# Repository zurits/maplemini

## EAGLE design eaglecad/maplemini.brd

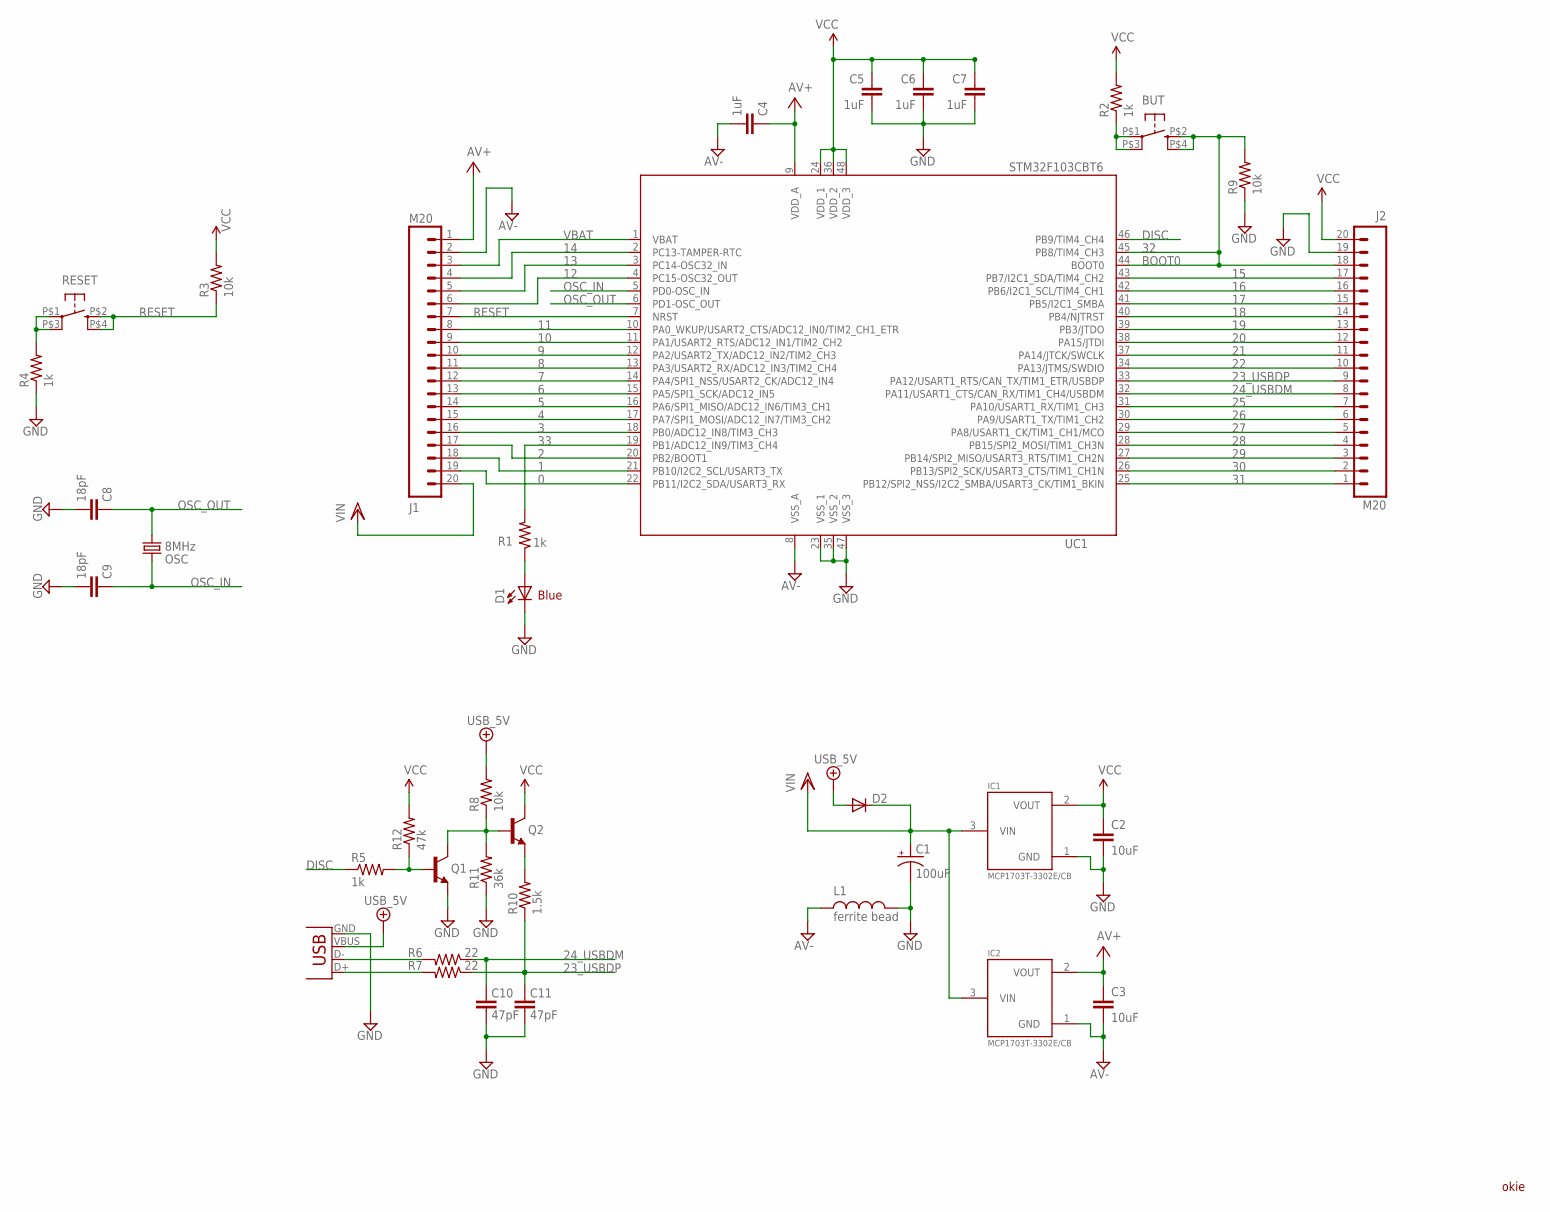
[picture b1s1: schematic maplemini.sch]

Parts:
BUT: KMR211GLFS; PUSHBUTTON-KMR241GLFS
C1: 100uF; EIA3216
C2, C3: 10uF; 0805
C4, C5, C6, C7: 1uF; C0402
C8, C9: 18pF; C0402
C10, C11: 47pF; C0402
D1: Blue; LED-1206
D2: DIODESOD; SOD-323
IC1, IC2: MCP1703T-3302E/CB; SOT23
J1, J2: M20; 1X20
L1: ferrite bead; 0603
OSC: 8MHz; CRYSTAL-SMD-5X3
Q1, Q2: NPN-BJT; SOT23
R1, R2, R4, R5: 1k; C0402
R3, R8, R9: 10k; C0402
R6, R7: 22; C0402
R10: 1.5k; C0402
R11: 36k; C0402
R12: 47k; C0402
RESET: KMR211GLFS; PUSHBUTTON-KMR241GLFS
UC1: STM32F103CBT6; LQFP48
X1: USB-MINIB

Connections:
0: J1.19, UC1.22 (PB11/I2C2_SDA/USART3_RX)
1: J1.18, UC1.21 (PB10/I2C2_SCL/USART3_TX)
2: J1.17, UC1.20 (PB2/BOOT1)
3: J1.16, UC1.18 (PB0/ADC12_IN8/TIM3_CH3)
4: J1.15, UC1.17 (PA7/SPI1_MOSI/ADC12_IN7/TIM3_CH2)
5: J1.14, UC1.16 (PA6/SPI1_MISO/ADC12_IN6/TIM3_CH1)
6: J1.13, UC1.15 (PA5/SPI1_SCK/ADC12_IN5)
7: J1.12, UC1.14 (PA4/SPI1_NSS/USART2_CK/ADC12_IN4)
8: J1.11, UC1.13 (PA3/USART2_RX/ADC12_IN3/TIM2_CH4)
9: J1.10, UC1.12 (PA2/USART2_TX/ADC12_IN2/TIM2_CH3)
10: J1.9, UC1.11 (PA1/USART2_RTS/ADC12_IN1/TIM2_CH2)
11: J1.8, UC1.10 (PA0_WKUP/USART2_CTS/ADC12_IN0/TIM2_CH1_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)
12: J1.6, UC1.4 (PC15-OSC32_OUT)
13: J1.5, UC1.3 (PC14-OSC32_IN)
14: J1.4, UC1.2 (PC13-TAMPER-RTC)
15: J2.17, UC1.43 (PB7/I2C1_SDA/TIM4_CH2)
16: J2.16, UC1.42 (PB6/I2C1_SCL/TIM4_CH1)
17: J2.15, UC1.41 (PB5/I2C1_SMBA)
18: J2.14, UC1.40 (PB4/NJTRST)
19: J2.13, UC1.39 (PB3/JTDO)
20: J2.12, UC1.38 (PA15/JTDI)
21: J2.11, UC1.37 (PA14/JTCK/SWCLK)
22: J2.10, UC1.34 (PA13/JTMS/SWDIO)
23_USBDP: C11.2, J2.9, R7.1, R10.1, UC1.33 (PA12/USART1_RTS/CAN_TX/TIM1_ETR/USBDP)
24_USBDM: C10.2, J2.8, R6.1, UC1.32 (PA11/USART1_CTS/CAN_RX/TIM1_CH4/USBDM)
25: J2.7, UC1.31 (PA10/USART1_RX/TIM1_CH3)
26: J2.6, UC1.30 (PA9/USART1_TX/TIM1_CH2)
27: J2.5, UC1.29 (PA8/USART1_CK/TIM1_CH1/MCO)
28: J2.4, UC1.28 (PB15/SPI2_MOSI/TIM1_CH3N)
29: J2.3, UC1.27 (PB14/SPI2_MISO/USART3_RTS/TIM1_CH2N)
30: J2.2, UC1.26 (PB13/SPI2_SCK/USART3_CTS/TIM1_CH1N)
31: J2.1, UC1.25 (PB12/SPI2_NSS/I2C2_SMBA/USART3_CK/TIM1_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)
32: BUT.P$2 (2), BUT.P$4 (4), J2.18, R9.2, UC1.44 (BOOT0), UC1.45 (PB8/TIM4_CH3)
33: R1.2, UC1.19 (PB1/ADC12_IN9/TIM3_CH4)
+5V/2: D2.2 (A), R8.2, X1.VBUS
AV+: C3.1, C4.1, IC2.2 (VOUT), J1.1, UC1.9 (VDD_A)
AV-: C3.2, C4.2, IC2.1 (GND), J1.2, L1.1, UC1.8 (VSS_A)
DGND: C1.C (-), C2.2, C5.2, C6.2, C7.2, C8.2, C9.2, C10.1, C11.1, D1.C, IC1.1 (GND), J2.19, L1.2, Q1.2 (E), R4.1, R9.1, R11.1, UC1.23 (VSS_1), UC1.35 (VSS_2), UC1.47 (VSS_3), X1.GND
DISC: R5.1, UC1.46 (PB9/TIM4_CH4)
unnamed: BUT.P$1 (1), BUT.P$3 (3), R2.1
unnamed: D1.A, R1.1
unnamed: R4.2, RESET.P$1 (1), RESET.P$3 (3)
unnamed: Q2.2 (E), R10.2
unnamed: R6.2, X1.D-
unnamed: R7.2, X1.D+
unnamed: Q1.3 (C), Q2.1 (B), R8.1, R11.2
unnamed: Q1.1 (B), R5.2, R12.1
OSC_IN: C9.1, OSC.3 (2), UC1.5 (PD0-OSC_IN)
OSC_OUT: C8.1, OSC.1, UC1.6 (PD1-OSC_OUT)
RESET: J1.7, R3.1, RESET.P$2 (2), RESET.P$4 (4), UC1.7 (NRST)
VBAT: J1.3, UC1.1 (VBAT)
VCC: C2.1, C5.1, C6.1, C7.1, IC1.2 (VOUT), J2.20, Q2.3 (C), R2.2, R3.2, R12.2, UC1.24 (VDD_1), UC1.36 (VDD_2), UC1.48 (VDD_3)
VIN: C1.A (+), D2.1 (C), IC1.3 (VIN), IC2.3 (VIN), J1.20

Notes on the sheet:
okie
BOOT0
Blue

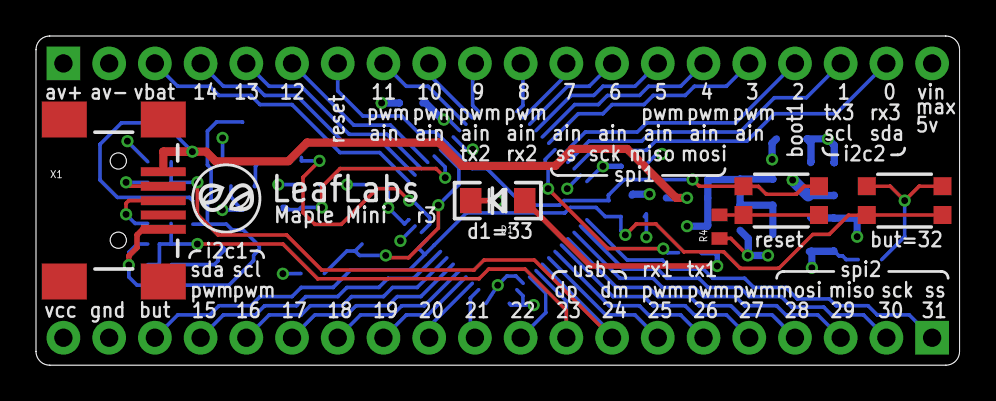
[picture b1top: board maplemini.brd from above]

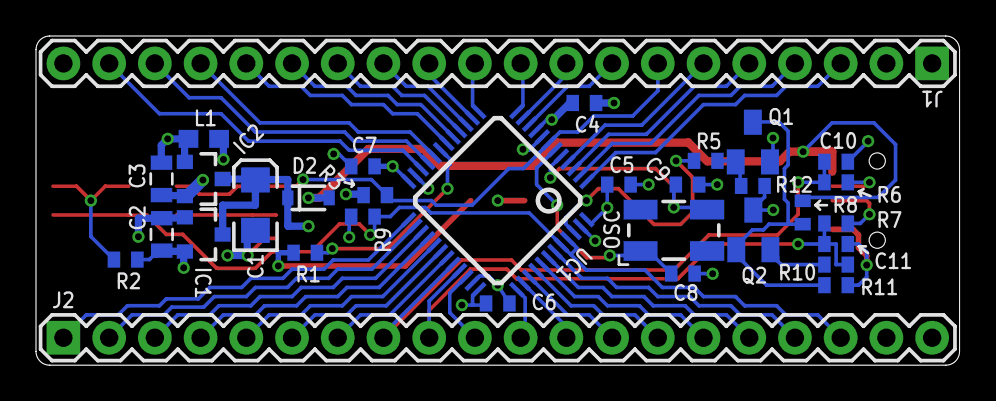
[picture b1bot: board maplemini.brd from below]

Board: 2 copper layers, 51.3 x 18.3 mm, 37 parts (32 on the bottom side), 53 nets.

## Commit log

2016-09-20 altium
2016-09-20 imported altium
